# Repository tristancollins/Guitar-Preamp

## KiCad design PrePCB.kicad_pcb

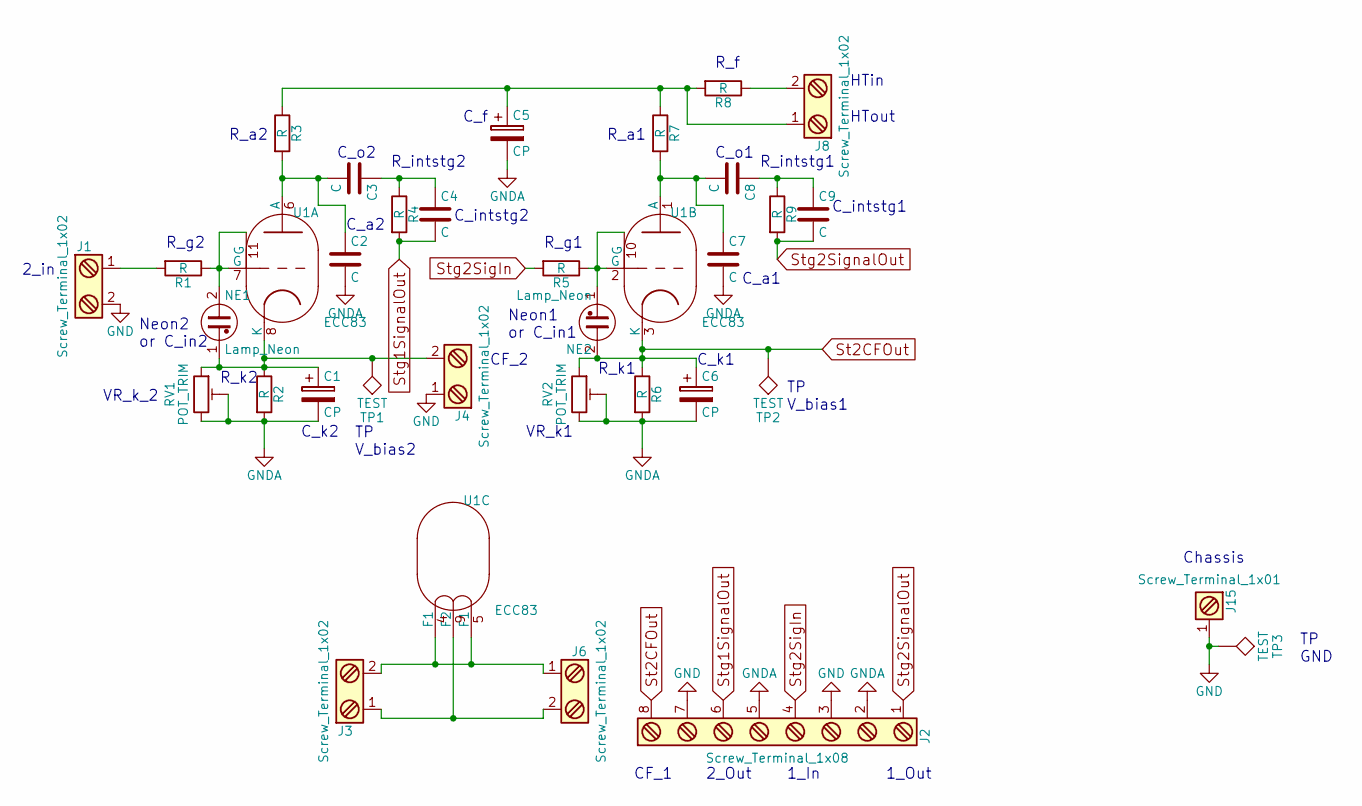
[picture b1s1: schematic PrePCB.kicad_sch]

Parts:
C1, C6: CP; CP_Radial_D5.0mm_P2.00mm
C2, C7: C; C_Disc_D7.5mm_W5.0mm_P7.50mm
C3, C8: C; C_Axial_L17.0mm_D6.5mm_P20.00mm_Horizontal
C4, C9: C; C_Axial_L3.8mm_D2.6mm_P12.50mm_Horizontal
C5: CP; CP_Radial_D18.0mm_P7.50mm; MPN UCA2W220MHD6
J1, J3, J4, J6, J8: Screw_Terminal_1x02; PhoenixContact_MCV-G_02x5.08mm_Vertical
J2: Screw_Terminal_1x08; PhoenixContact_MCV-G_08x5.08mm_Vertical
J15: Screw_Terminal_1x01; MountingHole_3.2mm_M3_Pad
NE1, NE2: Lamp_Neon; C_Disc_D7.5mm_W5.0mm_P7.50mm
R1, R3, R5, R7, R8: R; R_Axial_DIN0414_L11.9mm_D4.5mm_P15.24mm_Horizontal
R2, R4, R6, R9: R; R_Axial_DIN0207_L6.3mm_D2.5mm_P10.16mm_Horizontal
RV1, RV2: POT_TRIM; Potentiometer_Trimmer_Bourns_3339P_Horizontal
TP1, TP2, TP3: TEST; Test_Point_Keystone_5005-5009_Compact
U1: ECC83; VALVE-ECC-83-1-TC-Oct

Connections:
GND: J1.2, J2.3, J2.7, J4.1, J15.1, TP3.1
GNDA: C1.2, C2.2, C5.2, C6.2, C7.2, J2.2, J2.5, R2.2, R6.2, RV1.2, RV1.3, RV2.2, RV2.3
unnamed: C1.1, J4.2, NE1.1, R2.1, RV1.1, TP1.1, U1.8 (K)
unnamed: C2.1, C3.2, R3.2, U1.6 (A)
unnamed: C3.1, C4.1, R4.1
unnamed: C5.1, J8.1, R3.1, R7.1, R8.2
unnamed: C7.1, C8.2, R7.2, U1.1 (A)
unnamed: C8.1, C9.1, R9.1
unnamed: J1.1, R1.2
unnamed: J3.1, J6.2, U1.9 (F2)
unnamed: J3.2, J6.1, U1.4 (F1), U1.5 (F1)
unnamed: J8.2, R8.1
unnamed: NE1.2, R1.1, U1.7 (G), U1.11 (G)
unnamed: NE2.1, R5.1, U1.2 (G), U1.10 (G)
St2CFOut: C6.1, J2.8, NE2.2, R6.1, RV2.1, TP2.1, U1.3 (K)
Stg1SignalOut: C4.2, J2.6, R4.2
Stg2SigIn: J2.4, R5.2
Stg2SignalOut: C9.2, J2.1, R9.2

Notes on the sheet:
TP V_bias1
R_a1
R_k2
Neon1 or C_in1
C_o2
Chassis
R_intstg1
C_a2
C_o1
C_k1
CF_1
R_f
VR_k1
TP V_bias2
R_intstg2
R_g2
1_In
R_g1
HTout
VR_k_2
1_Out
CF_2
TP GND
C_a1
R_a2
2_Out
2_in
C_intstg2
R_k1
HTin
Neon2 or C_in2
C_f
C_k2
C_intstg1

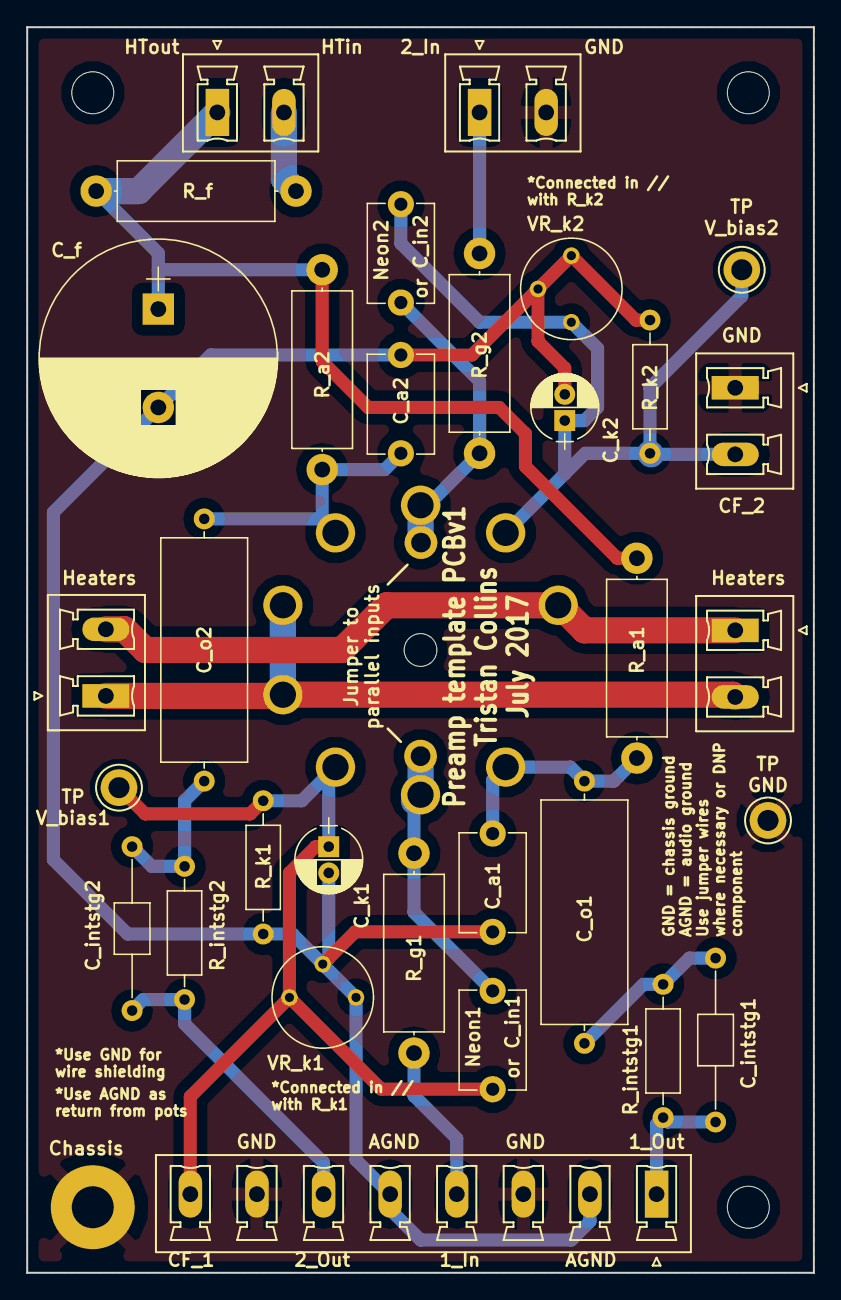
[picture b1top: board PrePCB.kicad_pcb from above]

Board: 2 copper layers, 60.0 x 95.0 mm, 33 parts (1 on the bottom side), 18 nets.

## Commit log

2020-04-26 1st upload of PCB files
2020-09-13 adding RS-274X gerbers
2025-06-16 updating to newer KiCad
